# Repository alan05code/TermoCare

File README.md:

# TermoCare
Termostato domestico Smart pensato per l'efficienza, sicurezza e precisione con integrazione tramite un'applicazione web e mobile.

Progettato, sviluppato e documentato in IMET S.r.l durante il PCTO scolastico 2023.
Presentato in azienda e agli Open Day scolastici.

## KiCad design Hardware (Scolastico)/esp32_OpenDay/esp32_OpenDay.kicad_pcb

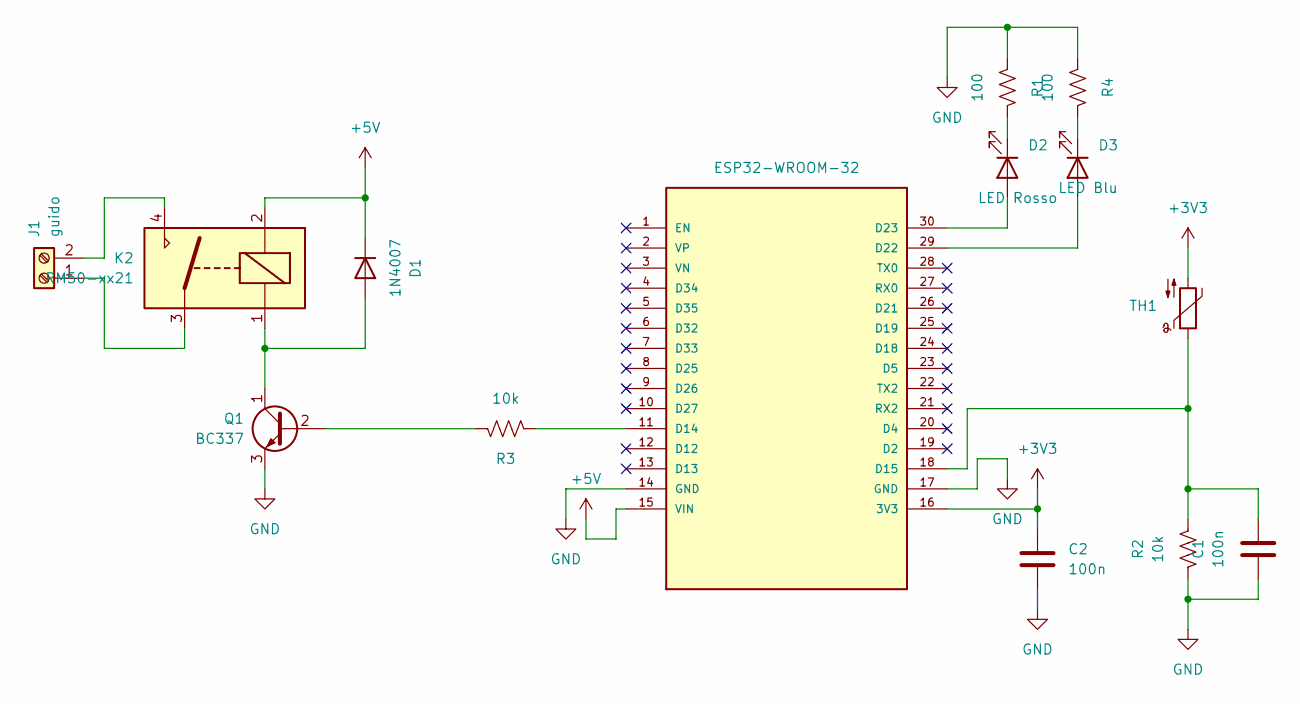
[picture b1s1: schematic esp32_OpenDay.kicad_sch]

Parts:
C1, C2: 100n; C_Disc_D7.0mm_W2.5mm_P5.00mm
D1: 1N4007; D_DO-41_SOD81_P10.16mm_Horizontal
D2: LED Rosso; LED_D5.0mm
D3: LED Blu; LED_D5.0mm
J1: guido; TerminalBlock_bornier-2_P5.08mm
K2: RM50-xx21; Relè_HF33F_CodiceRS_176-2640
Q1: BC337; TO-92L_Inline_Wide
R1, R4: 100; R_Axial_DIN0411_L9.9mm_D3.6mm_P15.24mm_Horizontal
R2, R3: 10k; R_Axial_DIN0411_L9.9mm_D3.6mm_P15.24mm_Horizontal
S1: ESP32-WROOM-32; MODULE_ESP32-WROOM-32; PARTREV N/A
TH1: Thermistor_NTC; R_Axial_DIN0207_L6.3mm_D2.5mm_P5.08mm_Vertical

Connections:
+3V3: C2.1, S1.16 (3V3), TH1.2
+5V: D1.1 (K), K2.2, S1.15 (VIN)
GND: C1.2, C2.2, Q1.3 (E), R1.2, R2.1, R4.2, S1.14 (GND), S1.17 (GND)
unnamed: D1.2 (A), K2.1, Q1.1 (C)
unnamed: D2.2 (A), S1.30 (D23)
unnamed: D2.1 (K), R1.1
unnamed: D3.2 (A), S1.29 (D22)
unnamed: D3.1 (K), R4.1
unnamed: J1.1, K2.3
unnamed: J1.2, K2.4
unnamed: Q1.2 (B), R3.1
unnamed: R3.2, S1.11 (D14)
unnamed: C1.1, R2.2, S1.18 (D15), TH1.1

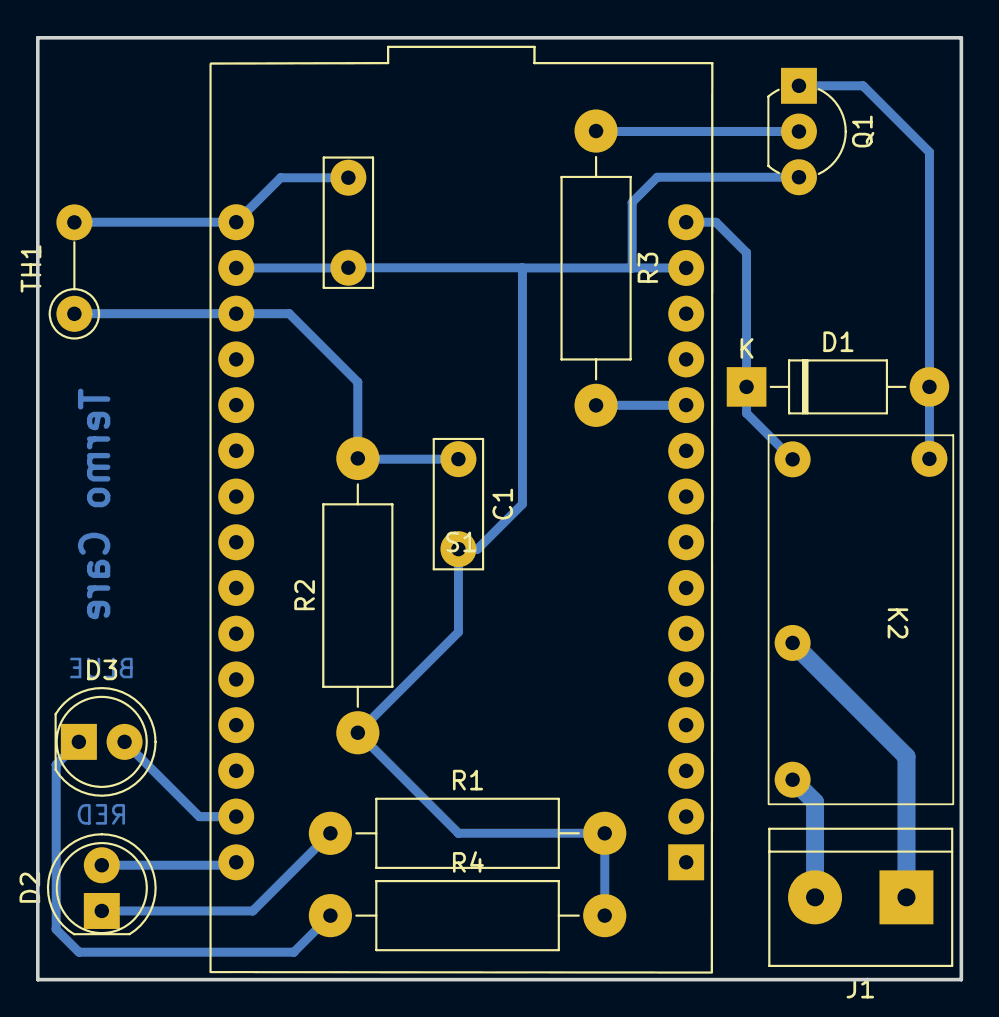
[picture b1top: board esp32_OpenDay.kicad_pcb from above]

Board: 2 copper layers, 51.3 x 52.3 mm, 14 parts (0 on the bottom side), 13 nets.

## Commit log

2025-02-07 Termo Care v1.0
